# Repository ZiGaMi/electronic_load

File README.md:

# Electronic Load Rev1.1 
# 
Supports constant current (CC), constant power (CP) and constant resistance modes (CR).

Power rating: 12 W        
Maximum load current: 1 A           
Maximum input voltage: 12 V
 
 Electronic load front:

Electronic load backside:

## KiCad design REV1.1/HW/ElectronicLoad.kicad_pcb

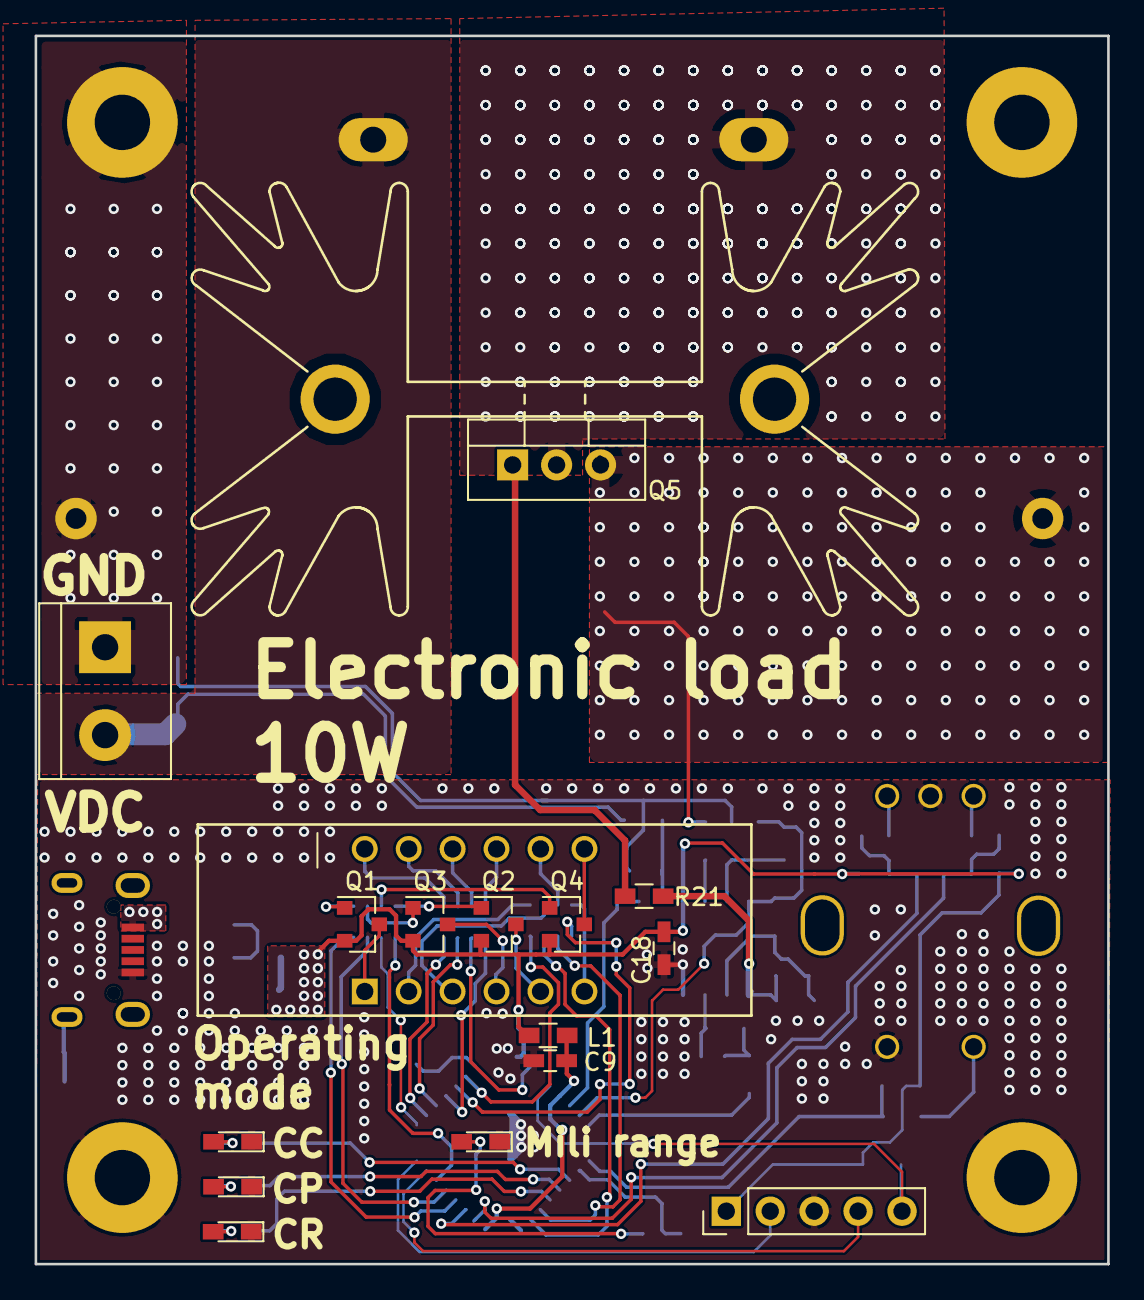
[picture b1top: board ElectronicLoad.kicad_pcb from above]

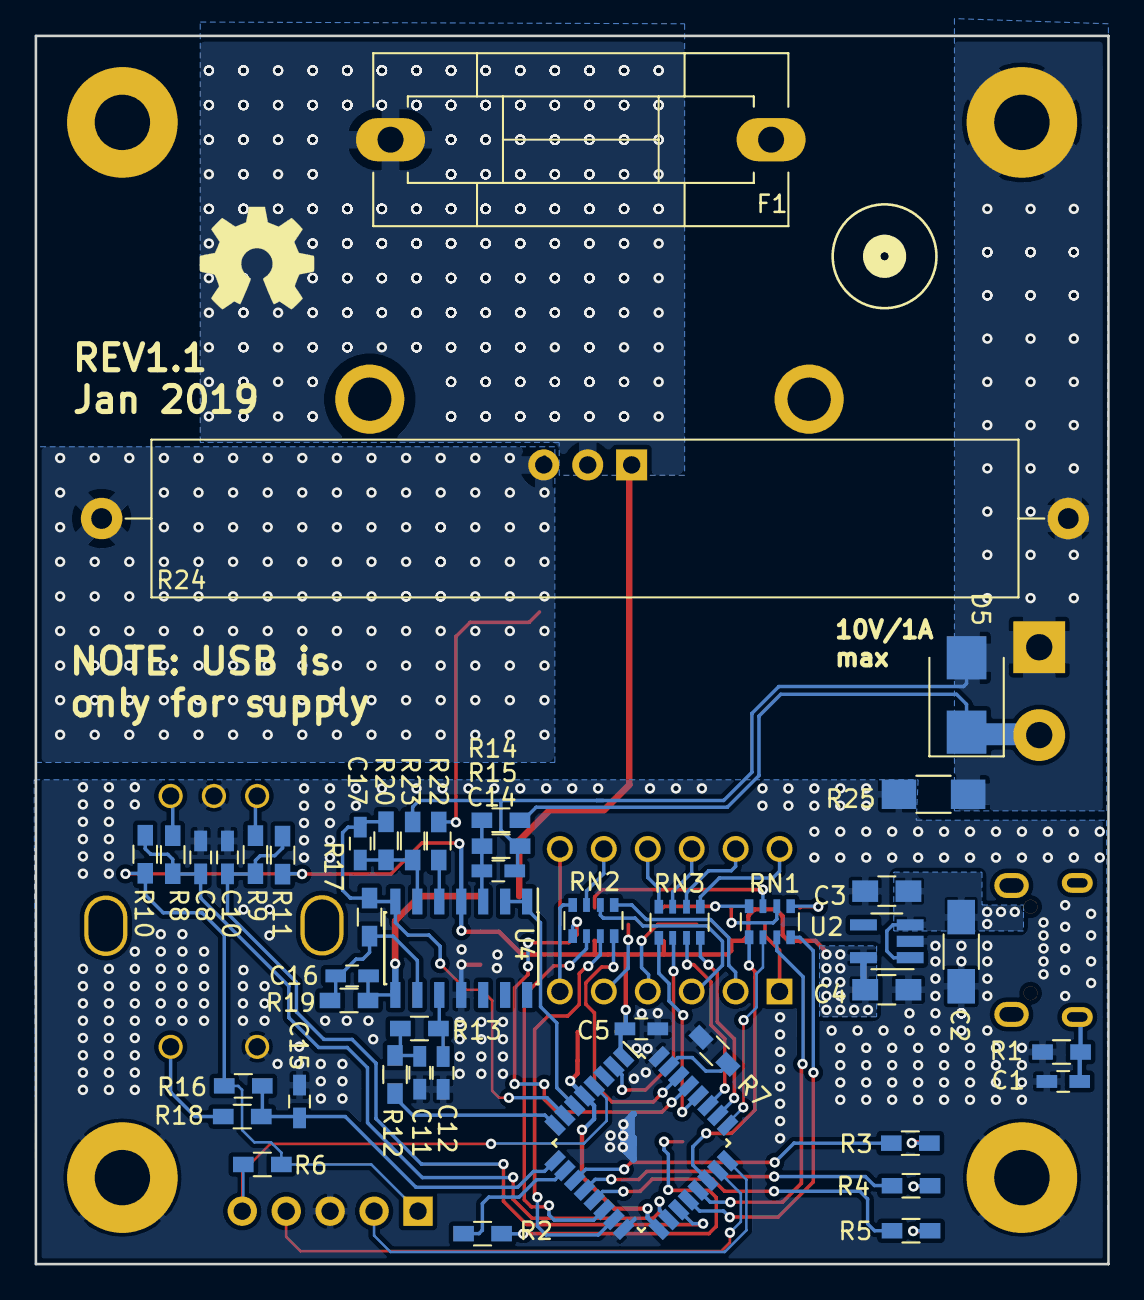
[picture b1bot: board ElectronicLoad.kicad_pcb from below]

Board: 2 copper layers, 62.0 x 71.0 mm, 67 parts (45 on the bottom side), 66 nets.

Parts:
C1, C16: 1n; C_0603_HandSoldering
C2: 4u7; C_1206_HandSoldering
C3, C4: 2u2; C_0805_HandSoldering
C5, C8, C9, C10, C11, C12, C14, C15, C18: 100n; C_0603_HandSoldering
C17: 10p; C_0603_HandSoldering
D1: m Suffix; LED_0603_HandSoldering
D2: CC; LED_0603_HandSoldering
D3: CP; LED_0603_HandSoldering
D4: CR; LED_0603_HandSoldering
D5: SMAJ12; D_SMB
F1: 1A; Fuseholder5x20_horiz_SemiClosed_Casing10x25mm
J1: Conn_01x05; Pin_Header_Straight_1x05_Pitch2.54mm
J2: USB_B_Micro; USBMicro_629105150521_WE
J3: Conn_01x02; TerminalBlock_bornier-2_P5.08mm
J4, J5, J6, J7: Conn_01x01; MountingHole_3.2mm_M3_Pad
L1: 100MHz; R_0603_HandSoldering
Q1, Q2, Q3, Q4: BC856A; SOT-23
Q5: TIP41A; TO-220-3_Vertical
R1: 1M; R_0603_HandSoldering
R2, R3, R4, R5: 3k3; R_0603_HandSoldering
R6: 47k; R_0603_HandSoldering
R7, R10, R11, R15, R16, R17, R22, R23: 10k; R_0603_HandSoldering
R8, R9, R12, R13, R18: 1k; R_0603_HandSoldering
R14: 27k; R_0603_HandSoldering
R19: DNS; R_0603_HandSoldering
R20: 20k; R_0603_HandSoldering
R21: 10R; R_0603_HandSoldering
R24: 1R / 10W; R_Axial_Power_L50.0mm_W9.0mm_P55.88mm
R25: 0R; R_1206_HandSoldering
RN1: 1k; R_Array_Convex_4x0603
RN2, RN3: 330R; R_Array_Convex_4x0603
SW1: EC11E09244BS
U1: CC56-12SEKWA; 7SegmentLCD_10x32
U2: NL1134; SOT-23-5_HandSoldering
U3: STM32F031K6Tx; LQFP-32_7x7mm_Pitch0.8mm
U4: AD8606; SOIC-14_3.9x8.7mm_Pitch1.27mm

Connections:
+3.3VA: C9.2, L1.2, U3.5, U3.17
+3V3: C4.1, C5.1, C18.1, J1.1, L1.1, Q1.2, Q2.2, Q3.2, Q4.2, R6.1, R10.1, R11.1, R16.1, U2.5, U3.1, U4.4
+5V: C2.1, C3.1, J2.1, U2.1, U2.3
/BASE_CA1: Q1.1, RN1.1
/BASE_CA2: Q3.1, RN1.2
/BASE_CA3: Q2.1, RN1.4
/BASE_CA4: Q4.1, RN1.3
/BTN: C15.1, R16.2, R18.2, U3.9
/CA1: Q1.3, U1.12
/CA2: Q3.3, U1.9
/CA3: Q2.3, U1.8
/CA4: Q4.3, U1.6
/Isense: C17.2, R17.1, R20.2, U3.7, U4.7
/LED_CC_MODE: R3.1, U3.11
/LED_CP_MODE: R4.1, U3.12
/LED_CR_MODE: R5.1, U3.13
/LED_PREFIX: R2.1, U3.10
/MCU_CA1: RN1.8, U3.20
/MCU_CA2: RN1.7, U3.21
/MCU_CA3: RN1.5, U3.22
/MCU_CA4: RN1.6, U3.25
/MCU_a: RN2.8, U3.30
/MCU_b: RN2.5, U3.29
/MCU_c: RN3.5, U3.28
/MCU_d: RN3.7, U3.27
/MCU_dpx: RN3.6, U3.2
/MCU_e: RN3.8, U3.26
/MCU_f: RN2.7, U3.15
/MCU_g: RN2.6, U3.14
/NRST: J1.5, R6.2, U3.4
/PWM: R12.1, U3.8
/SWCLK: J1.2, U3.24
/SWDIO: J1.4, U3.23
/Usense: U3.6, U4.1, U4.2
/a: RN2.1, U1.11
/b: RN2.4, U1.7
/c: RN3.4, U1.4
/d: RN3.2, U1.2
/dpx: RN3.3, U1.3
/e: RN3.1, U1.1
/f: RN2.2, U1.10
/g: RN2.3, U1.5
/phase_A: C8.1, R8.1, R10.2, U3.18
/phase_B: C10.1, R9.1, R11.2, U3.19
GND: C1.2, C2.2, C3.2, C4.2, C5.2, C8.2, C9.1, C10.2, C11.1, C12.1, C15.2, C18.2, D1.1, D2.1, D3.1, D4.1, J1.3, J2.5, J5.1, J7.1, R1.2, R7.1, R25.1, SW1.C, SW1.S2, U2.2, U3.16, U3.32, U4.11
GNDPWR: C14.2, D5.2, J3.1, J4.1, R15.2, R23.1, R24.2, R25.2
unnamed: C1.1, J2.6, R1.1
unnamed: C11.2, R12.2, R13.1
unnamed: C12.2, R13.2, U4.10
unnamed: C14.1, R14.2, R15.1, U4.3
unnamed: C16.1, R19.1, R21.2, U4.8
unnamed: C16.2, R17.2, R19.2, U4.9
unnamed: C17.1, R20.1, R23.2, U4.6
unnamed: D1.2, R2.2
unnamed: D2.2, R3.2
unnamed: D3.2, R4.2
unnamed: D4.2, R5.2
unnamed: F1.1, Q5.2
unnamed: Q5.1, R21.1
unnamed: Q5.3, R22.1, R24.1
unnamed: R7.2, U3.31
unnamed: R8.2, SW1.A
unnamed: R9.2, SW1.B
unnamed: R18.1, SW1.S1
unnamed: R22.2, U4.5
VBUS: D5.1, F1.2, J3.2, R14.1

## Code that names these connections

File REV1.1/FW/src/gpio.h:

/*
 * gpio.h
 *
 *  Created on: 26.10.2018
 *      Author: ziga.miklosic
 */

#ifndef GPIO_H_
#define GPIO_H_

#include "stm32f031x6.h"


/*
 * 		ADC inputs
 * 	Pins: 	PA0 -> Usense
 * 			PA1 -> Isense
 */
#define SENSE_PORT		( GPIOA )
#define VOL_SENSE_bp	( 0ul )
#define CUR_SENSE_bp	( 1ul )


/*
 * 		TIMER output
 * 	Pin: 	PA2 -> pwm for reference generation
 */
#define CUR_REF_PORT		( GPIOA )
#define CUR_REF_bp		( 2ul )


/*
 * 		PUSH BUTTON ( rotary encoder )
 * 	Pin:	PA3 -> buttons
 *
 * 	NOTE: Active low
 */
#define BUTTON_PORT		( GPIOA )
#define BUTTON_bp		( 3ul )
#define BUTTON_TIMEOUT	( float )	( 1.0f )	// sec


/*
 * 		LEDs INDICATIORS
 *	Pins: 	PA4 -> Range prefix
 *			PA5 -> CC mode
 *			PA6 -> CP mode
 *			PA7 -> CR mode
 */
#define LED_PORT		( GPIOA )
#define LED_RANGE_bp	( 4ul )
#define LED_CC_bp		( 5ul )
#define LED_CP_bp		( 6ul )
#define LED_CR_bp		( 7ul )

/*
 *
 * 		TIMER input ( rotary encoder )
 * 	Pin:	PA8	-> phase A
 * 			PA9 -> phase B
 */
#define ENCODER_PORT	( GPIOA )
#define PHASE_A_bp		( 8ul )
#define PHASE_B_bp		( 9ul )


/*
 * 		SEVEN SEGMENT DISPLAY
 * 	Pin: 	PA10 -> CA1
 * 			PA11 -> CA2
 * 			PA12 -> CA3
 * 			PA13 -> CA4 (SWCLK)
 * 			PB0 -> g
 * 			PB1 -> f
 * 			PB3 -> e
 * 			PB4 -> d
 * 			PB5 -> c
 * 			PB6 -> b
 * 			PB7 -> a
 */
#define CA_PORT		( GPIOA )
#define SEG_PORT	( GPIOB )
#define CA1_bp		( 10ul )
#define CA2_bp		( 11ul )
#define CA3_bp		( 12ul )
#define CA4_bp		( 15ul )
#define SEG_G_bp	( 0ul )
#define SEG_F_bp	( 1ul )
#define SEG_E_bp	( 3ul )
#define SEG_D_bp	( 4ul )
#define SEG_C_bp	( 5ul )
#define SEG_B_bp	( 6ul )
#define SEG_A_bp	( 7ul )

#define DPX_PORT	( GPIOF )
#define DPX_bp		( 0ul )


/*
 * 	GPIO Functions
 */
void GpioInit(void);
void GpioPinOn(GPIO_TypeDef*, uint8_t);
void GpioPinOff(GPIO_TypeDef*, uint8_t);
void GpioPinToggle(GPIO_TypeDef*, uint8_t);

void LedsOff(void);


#endif /* GPIO_H_ */

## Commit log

2019-01-28 new file: ElectronicLoadDrv.c new file: ElectronicLoadDrv.h new file: RotaryEncoderDrv.c new file: RotaryEncoderDrv.h new file: SevenSegmentDrv.c new file: SevenSegmentDrv.h new file: adc.c new file: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
2019-01-28 new file: ElectronicLoad.kicad_pcb new file: ElectronicLoad.pro new file: ElectronicLoad.sch
2019-01-28 new file: Docs/ElectronicLoad_REV1.1_schematic.pdf
2019-05-05 modified: README.md
